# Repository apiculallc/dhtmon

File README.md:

## Objective

To create a small, contained and "offline" temperature / humidity monitoring system for hard-to-reach places like attics, garages, crawlspaces, sheds etc.

## Requirements

- GNU make
- GCC
- [ESP-IDF toolkit](https://docs.espressif.com/projects/esp8266-rtos-sdk/en/latest/)
- Docker

### Hardware / BOM

| Part | Quantity | Price ( approx ) | Link |
|------|----------|------------------|--|
| ESP8266 | 1        | $ 1.20           | https://www.ebay.com/itm/185185809189?var=692941428853 |
| DHT22/AM2302 | 1        | $ 3.33           | https://www.amazon.com/gp/product/B08TGQY64D/ref=ppx_yo_dt_b_search_asin_title?ie=UTF8&th=1 |
| AMS1117 | 1 | $ 0.35           | https://www.amazon.com/gp/product/B08CDMZMDN/ref=ppx_yo_dt_b_search_asin_title?ie=UTF8&psc=1 |
|  Capacitor 10mF | 1 |  $ 0.03  | https://www.amazon.com/gp/product/B087785H1J/ref=ppx_yo_dt_b_search_asin_title?ie=UTF8&psc=1 |
| USB 2.0 Type A Male Socket Connector Jack Port | 1 |  $ 0.11  | https://www.amazon.com/gp/product/B07QY6GJ6M/ref=ppx_yo_dt_b_search_asin_title?ie=UTF8&th=1 |
| Push button 6mm | 1 |  $ 0.07  | https://www.ebay.com/itm/312535619242 |
| SMD Resistor 10kOhm | 4 |  $ 0.03  | https://www.ebay.com/itm/163584740236 |
| PCB | 1 |  $ 2.57  | https://oshpark.com/ |

### Total: ~$8 per board

#### You can also order the board at our blog at https://www.apicula.com/blog/monitoring-temperature-and-humidity-in-unoccupied-zones/

## Build

Clone the repository as `git clone --recurse-submodules -j8 git://github.com/apiculallc/dht.git`

### ESP8266 firmware

- follow the instructions to setup the [ESP-IDF toolchain](https://docs.espressif.com/projects/esp8266-rtos-sdk/en/latest/get-started/index.html#setup-toolchain)
- edit `nvs.csv` file to specify the location and name of the sensor. You can skip this step and configure everything using WiFi setup
  - `wifi_ssid` - name of the access point to connect to
  - `wifi_password` - WiFi password 
  - `app_location` - sensor location ( attic, garage etc )
  - `app_mqtt_url` - the URL to MQTT broker - this is typically the same location as where you will have InfluxDB and the Hub running
- run `make all` to build the flash image
- run `make flash` to flash the partition table
- run `make nvs` to flash the NVS table with the probe settings

### Hub
- change directory to `go`
- run `make` to build the executable for your platform - you'll need to have [Golang](https://go.dev/) installed
- run `make docker` to build a docker image

### Deployment

With use of [Docker Compose](https://docs.docker.com/compose/) everything shall be straightforward:

```bash
docker-compose up -d
```

That should create all the necessary pieces

For step-by-step instructions please read below.

#### Start Mosquitto

Create a config file `mosquitto.conf` with the content:

```
persistence false

log_dest stdout
log_type warning
log_timestamp true
connection_messages true

listener 1883

## Authentication ##
allow_anonymous true

```
 Then run Mosquitto in Docker as:
```bash
docker run --name mosquitto \
 -d --restart=unless-stopped \ 
 -p 1883:1883 \
 -v `pwd`/mosquitto.conf:/mosquitto/config/mosquitto.conf \
eclipse-mosquitto
```
This will expose Mosquitto on port 1883 and allow anonymous access.
#### Start InfluxDB

Run in Docker as:

```bash
docker run -d -p 8086:8086 \
  --name=dhtmon-influx \
  --restart=unless-stopped \
  -v "/opt/data/influxdb-dhtmon:/var/lib/influxdb2" \
  -v "/opt/config/influxdb-dhtmon:/etc/influxdb2" \
  -e DOCKER_INFLUXDB_INIT_MODE=setup \
  -e DOCKER_INFLUXDB_INIT_USERNAME=admin \
  -e DOCKER_INFLUXDB_INIT_PASSWORD=admin123456 \
  -e DOCKER_INFLUXDB_INIT_ORG=home \
  -e DOCKER_INFLUXDB_INIT_BUCKET=dhtmon \
  -e `DOCKER_INFLUXDB_INIT_ADMIN_TOKEN=token123456 \
  influxdb:2.7-alpine
```

This will provision the instance of InfluxDB locally that exposes port 8086 if you need to check on the connection string.

#### Start Hub

In order to test that the Hub works well, you may use the following command ( assuming you have Golang installed ):
```
APP_MQTT_BROKER=mqtt://127.0.0.1:1883 \
INFLUX_DB=http://127.0.0.1:8086 \
INFLUX_TOKEN=token123456 \
go run main.go
```
This will build the project and start the service. Normal output should look like:
```
DB http://127.0.0.1:8086
TOKEN token123456
2024/07/03 10:11:12 started processing topics
```

Now the system is ready to receive data from the sensors.

Alternatively, use Docker container that you built as:

```
docker run --rm \
  -it \
  -e APP_MQTT_BROKER=mqtt://mosquitto:1883 \
  -e INFLUX_DB=http://dhtmon-influx:8086 \
  -e INFLUX_TOKEN=token123456 \
  --link dhtmon-influx \
  --link mosquitto \
  ghcr.io/apiculallc/dhtmon:latest  

DB http://dhtmon-influx:8086
TOKEN token123456
2024/07/04 10:11:12 started processing topics
```

If the Hub is running without any error, you can automate the process with

```bash
docker run --restart=unless-stopped \
  -it \
  -e APP_MQTT_BROKER=mqtt://mosquitto:1883 \
  -e INFLUX_DB=http://dhtmon-influx:8086 \
  -e INFLUX_TOKEN=token123456 \
  --link dhtmon-influx \
  --link mosquitto \
  ghcr.io/apiculallc/dhtmon:latest  
```
This will start the hub in daemon mode.
### Start sensor

Just plug the sensor - it shall connect to the WiFi access point and then start sending data to the topics. 

## Post-installation steps

There is no LCD screens or anything that can be easily observed by a human being, so it is hard to tell whether the system works as expected. The joy of system level programming! So we shall be creative about our means to verify the functionality.

The easiest way to test that everything works as expected is to use an MQTT client and subscribe to the topics. For example, using [`mqtt-shell`](https://github.com/rainu/mqtt-shell):
```bash
mqtt-shell -b mqtt://127.0.0.1:1883
>> sub /home/sensor/#
/home/sensor/attic/temp | 29.3
/home/sensor/attic/humid | 55.9
/home/sensor/garage/temp | 27.1
/home/sensor/garage/humid | 56.1
```

This indicates that sensors actually transmits data.

To verify that we actually receive something in the database ( InfluxDB ) we need to connect to the DB and run a few queries. As we have the installation that exposes ports 8086 - we can simply open [http://127.0.0.1:8086](http://127.0.0.1:8086) and use login  `admin` and password `admin123456` to peek into the storage.  Choose `Buckets` and select `dhtmon`:

From here, you may want to configure Grafana.

#### [Grafana](https://grafana.com/)

This is fairly sophisticated and powerful tool for monitoring and alerting in DevOps world. We're going to use it to render the charts and get the most recent data from the set of probes that we setup.

###### Installation

Pull the docker image and link it to a container that runs InfluxDB.

```bash
docker run --restart=unless-stopped \
	-e GF_SECURITY_ADMIN_USER=admin \
	-e GF_SECURITY_ADMIN_PASSWORD=admin123 \
	--link influxdb \
	-p 3000:3000 \
	-v ./grafana/provisioning/:/etc/grafana/provisioning/ \
	-v ./grafana/dashboards/:/var/lib/grafana/dashboards/ \
	grafana/grafana:10.0.10
```

This will populate the default data source with the InfluxDB and then create a dashboard that shall look like following ( if you have some data in there from the sensors ).

To "prime" some data and verify that this part works fine, you can use the following command:

```bash
cat <<EOF | mqtt-shell -b mqtt://127.0.0.1:1883
pub /home/sensor/garage/temp 32.1
pub /home/sensor/garage/humid 55.0
pub /home/sensor/attic/humid 35.0
pub /home/sensor/attic/temp 40.0
pub /home/sensor/crawlspace/temp 27.0
pub /home/sensor/crawlspace/humid 65.0
EOF
Successfully connected to mqtt broker.
```

The result can look like:

After you run that for some time, the result will be much more interesting:

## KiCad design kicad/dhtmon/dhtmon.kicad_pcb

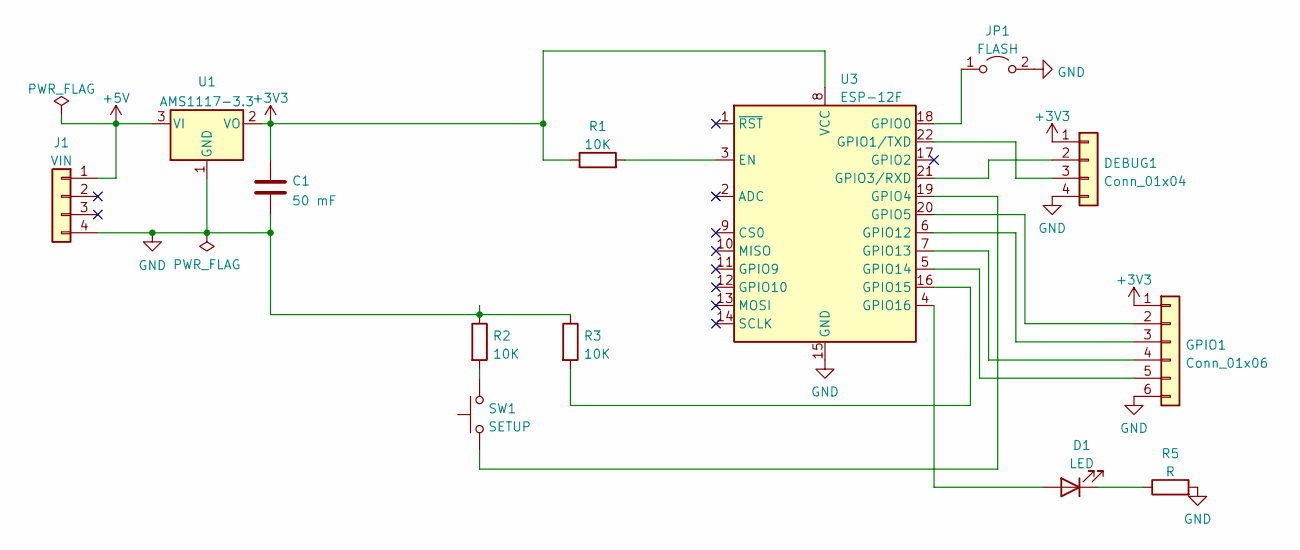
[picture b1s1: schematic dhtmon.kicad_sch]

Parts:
C1: 50 mF; C_Disc_D5.0mm_W2.5mm_P5.00mm
D1: LED; LED_D3.0mm
DEBUG1: Conn_01x04; PinHeader_1x04_P2.54mm_Vertical
GPIO1: Conn_01x06; PinHeader_1x06_P2.54mm_Vertical
J1: VIN; USB_A_CNCTech_1001-011-01101_Horizontal
JP1: FLASH; PinHeader_1x02_P2.54mm_Vertical
R1, R2, R3: 10K; R_0805_2012Metric
R5: R; R_0805_2012Metric
SW1: SETUP; SW_PUSH_6mm
U1: AMS1117-3.3; TO-262-3_Vertical
U3: ESP-12F; ESP-12E

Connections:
+3V3: C1.1, DEBUG1.1, GPIO1.1, R1.1, U1.2 (VO), U3.8 (VCC)
+5V: J1.1, U1.3 (VI)
GND: C1.2, DEBUG1.4, GPIO1.6, J1.4, JP1.2 (B), R2.1, R3.1, R5.2, U1.1 (GND), U3.15 (GND)
unnamed: D1.2 (A), U3.4 (GPIO16)
unnamed: D1.1 (K), R5.1
unnamed: DEBUG1.2, U3.21 (GPIO3/RXD)
unnamed: DEBUG1.3, U3.22 (GPIO1/TXD)
unnamed: GPIO1.2, U3.20 (GPIO5)
unnamed: GPIO1.3, U3.6 (GPIO12)
unnamed: GPIO1.4, U3.7 (GPIO13)
unnamed: GPIO1.5, U3.5 (GPIO14)
unnamed: JP1.1 (A), U3.18 (GPIO0)
unnamed: R2.2, SW1.2
unnamed: R1.2, U3.3 (EN)
unnamed: SW1.1, U3.19 (GPIO4)
unnamed: R3.2, U3.16 (GPIO15)

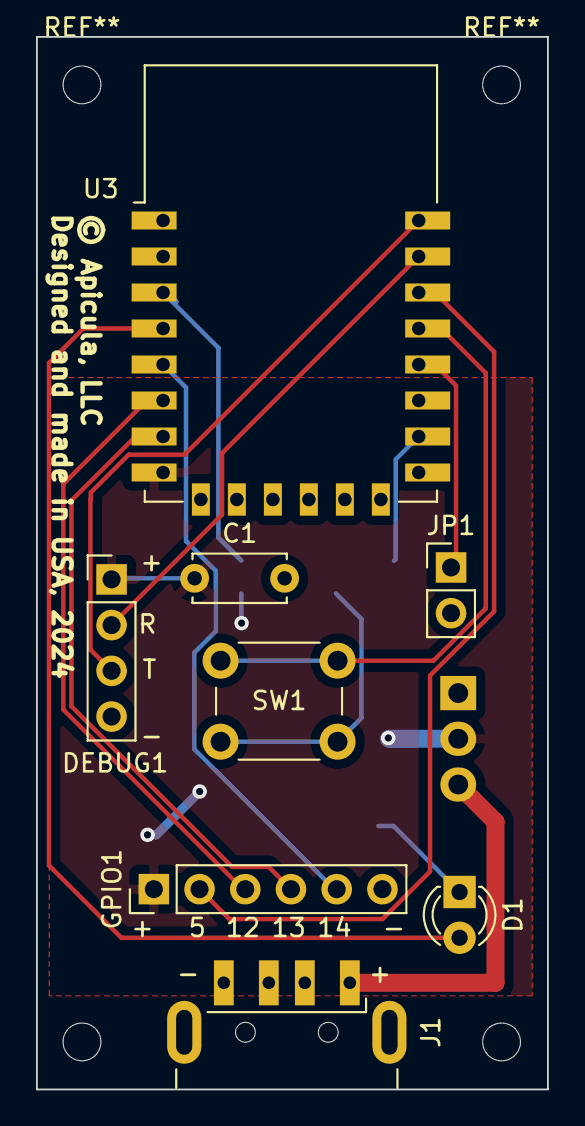
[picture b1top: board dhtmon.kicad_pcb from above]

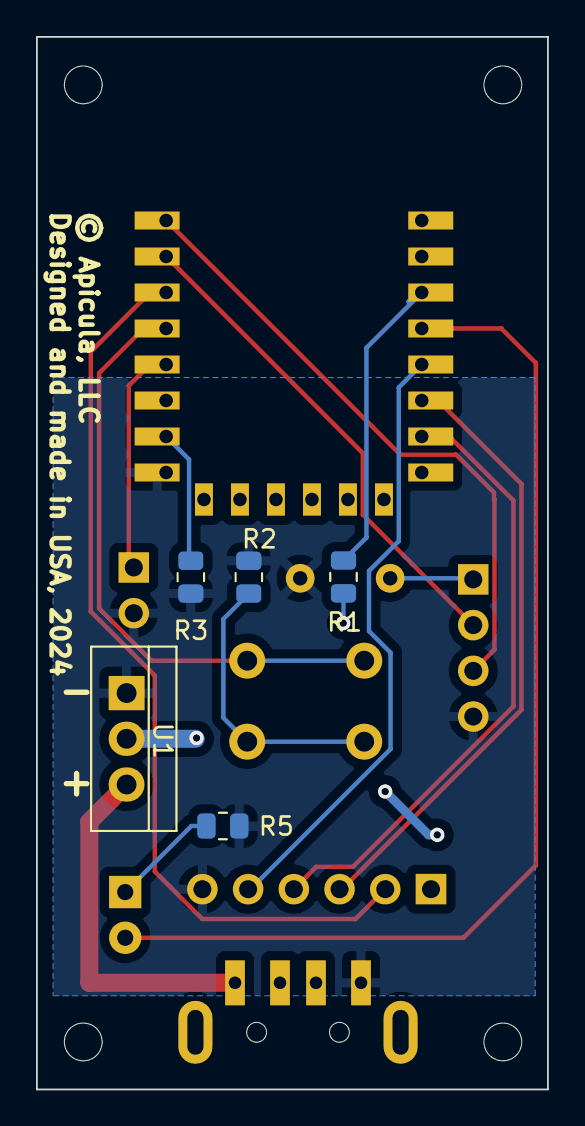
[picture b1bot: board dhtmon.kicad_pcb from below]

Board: 2 copper layers, 28.4 x 58.5 mm, 15 parts (5 on the bottom side), 16 nets.

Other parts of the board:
REF1, REF2: MountingHole_2.1mm

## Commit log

2024-07-06 Added web config and AP mode for easy setup.
2024-07-06 Set values as floats.
2024-07-06 Added proper path to include submodule component.
2024-07-06 Restart on Wifi failures.
    Fix float processing issue / snprintf.
2024-07-06 Added docs and instructions.
2024-07-06 MQTT publishing of the sensor data.
2024-07-06 Added demo resources for local testing using Docker Compose.
2024-07-06 Assign GPIO for button
    Can be altered between GPIO4/GPIO5 depending on wiring schema.
2024-07-06 Initial import.
2024-07-06 Added ESP-LIB submodule
2024-07-08 Added 3D models and KiCAD schematics.
2024-07-08 Added 3D model for the case.
2024-08-11 Added BOM and link to the blog.

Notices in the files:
kicad/dhtmon/dhtmon.kicad_pcb:
© Apicula, LLC
